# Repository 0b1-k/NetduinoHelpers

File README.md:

The 'Netduino Helpers' is a C# library providing hardware drivers and utility classes supporting the following:

* Analog joysticks
* Interrupt-driven push-button
* Real-time clock (DS1307)
* 8*8 LED matrix
* AdaFruit ILI932x TFT display
* AdaFruit SSD1306 OLED display
* AdaFruit ST7735 TFT display
* AdaFruit VC0706 Camera
* AdaFruit ST7565 Negative LCD display
* AdaFruit LPD8806 LED strip driver
* Sharp GP2Y0A21YK0F Distance Measuring Sensor
* Shift registers (74hc595)
* Runtime assembly & resource loader
* Bitmaps & Bitmap Compositions
* HiTec HS6635HB servo driver
* Serial Interface Builder
* LED matrix driver (Maxim7219 or compatible)
* RTTL sound support (ringtones)
* Variable / Fixed type font rendering
* 16x16 icon rendering
* Basic type serialization / deserialization
* Trigonometry library (exMath-based)
* Lightweight JSON parser (parsing from stream & string)
* Virtual Memory support
* PIX-6T4 console bootloader and games

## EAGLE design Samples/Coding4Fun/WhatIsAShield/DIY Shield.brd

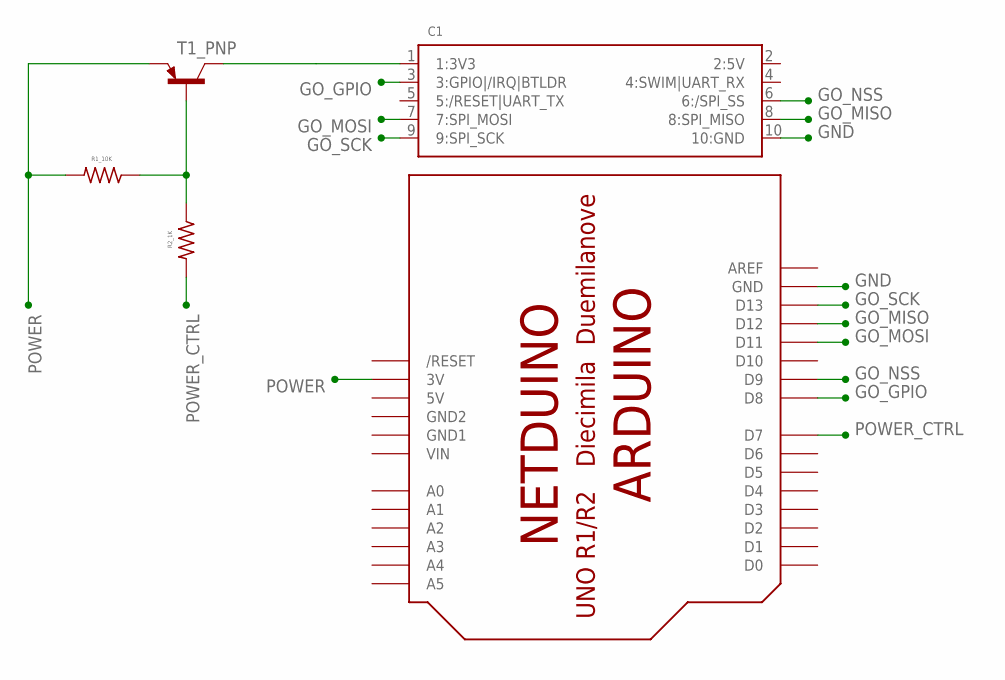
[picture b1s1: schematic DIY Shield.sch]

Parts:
C1: GO_CONNECTOR; FCI-1.27X1.27MM_10PIN_HEADER_SHROUDED_SMT
NETDUINOSHIELD: ARDUINOUNO; ARDUINO
R1_10K, R2_1K: RESISTOR_0805; 0805_NO_POLARITY
T1_PNP: -PNP-TO92; TO92

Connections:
2:5V: C1.2 (2:5V)
5V: NETDUINOSHIELD.5V
GND: C1.10 (10:GND), NETDUINOSHIELD.GND
GND1: NETDUINOSHIELD.GND1
GND2: NETDUINOSHIELD.GND2
GO_GPIO: C1.3 (3:GPIO|/IRQ|BTLDR), NETDUINOSHIELD.D8
GO_MISO: C1.8 (8:SPI_MISO), NETDUINOSHIELD.D12
GO_MOSI: C1.7 (7:SPI_MOSI), NETDUINOSHIELD.D11
GO_NSS: C1.6 (6:/SPI_SS), NETDUINOSHIELD.D9
GO_SCK: C1.9 (9:SPI_SCK), NETDUINOSHIELD.D13
unnamed: C1.1 (1:3V3), T1_PNP.3 (C)
unnamed: R1_10K.1, R2_1K.1, T1_PNP.2 (B)
POWER: NETDUINOSHIELD.3V, R1_10K.2, T1_PNP.1 (E)
POWER_CTRL: NETDUINOSHIELD.D7, R2_1K.2
VIN: NETDUINOSHIELD.VIN

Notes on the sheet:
NETDUINO

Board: 2 copper layers, 5 parts (0 on the bottom side), 10 nets, no tracks yet.

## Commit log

2015-04-07 Project migrated from CodePlex
2015-04-07 Added README.md
2015-04-08 Hardware schematics, board layout and laser-cut case design file
